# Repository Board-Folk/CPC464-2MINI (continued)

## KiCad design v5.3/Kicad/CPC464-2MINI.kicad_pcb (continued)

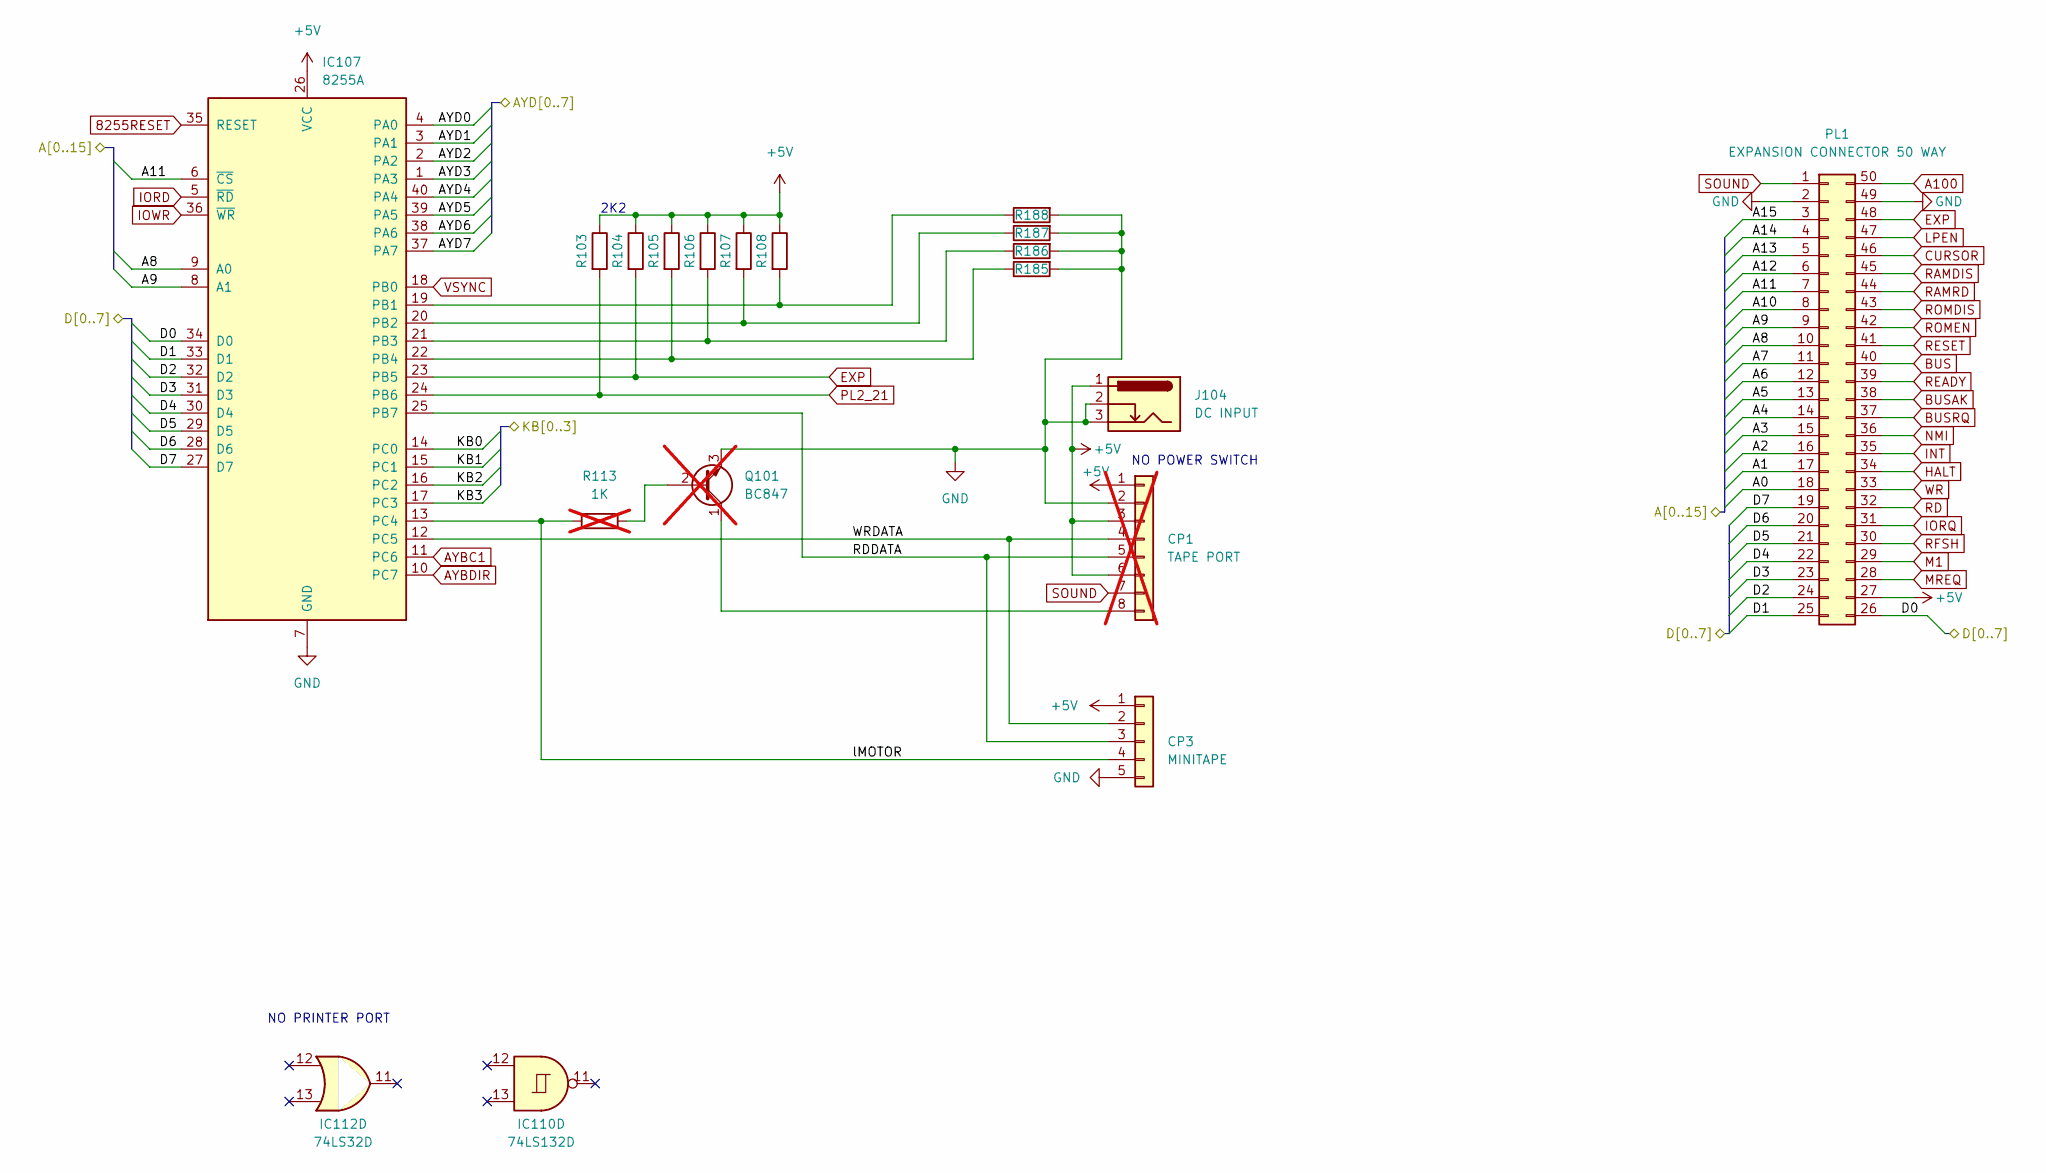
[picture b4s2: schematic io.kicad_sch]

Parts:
CP1: TAPE PORT; PinHeader_1x08_P2.54mm_Vertical; not fitted
CP3: MINITAPE; PinHeader_1x05_P2.54mm_Vertical
IC107: 8255A; DIP-40_W15.24mm
IC110: 74LS132D; SOIC-14_3.9x8.7mm_P1.27mm
IC112: 74LS32D; SOIC-14_3.9x8.7mm_P1.27mm
J104: DC INPUT; BarrelJack_Horizontal
PL1: EXPANSION CONNECTOR 50 WAY; EXPANSION_IDC_ANONYMISED
Q101: BC847; TO-92_Inline; not fitted
R103, R104, R105, R106, R107, R108: 2K2; R_0805_2012Metric; LCSC C114561
R113: 1K; R_0805_2012Metric; LCSC C482939; not fitted
R185, R186, R187, R188: 0R; R_0805_2012Metric; LCSC C114561

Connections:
8255RESET: IC107.35 (RESET); also elsewhere on the board
+5V: CP1.1, CP1.3, CP1.6, CP3.1, IC107.26 (VCC), J104.1, PL1.27, R103.1, R104.1, R105.1, R106.1, R107.1, R108.1; also elsewhere on the board
/CPU/A0: PL1.18; also elsewhere on the board
/CPU/A1: PL1.17; also elsewhere on the board
/CPU/A2: PL1.16; also elsewhere on the board
/CPU/A3: PL1.15; also elsewhere on the board
/CPU/A4: PL1.14; also elsewhere on the board
/CPU/A5: PL1.13; also elsewhere on the board
/CPU/A6: PL1.12; also elsewhere on the board
/CPU/A7: PL1.11; also elsewhere on the board
/CPU/A8: IC107.9 (A0), PL1.10; also elsewhere on the board
/CPU/A9: IC107.8 (A1), PL1.9; also elsewhere on the board
/CPU/A10: PL1.8; also elsewhere on the board
/CPU/A11: IC107.6 (~CS), PL1.7; also elsewhere on the board
/CPU/A12: PL1.6; also elsewhere on the board
/CPU/A13: PL1.5; also elsewhere on the board
/CPU/A14: PL1.4; also elsewhere on the board
/CPU/A15: PL1.3; also elsewhere on the board
/CPU/D0: IC107.34 (D0), PL1.26; also elsewhere on the board
/CPU/D1: IC107.33 (D1), PL1.25; also elsewhere on the board
/CPU/D2: IC107.32 (D2), PL1.24; also elsewhere on the board
/CPU/D3: IC107.31 (D3), PL1.23; also elsewhere on the board
/CPU/D4: IC107.30 (D4), PL1.22; also elsewhere on the board
/CPU/D5: IC107.29 (D5), PL1.21; also elsewhere on the board
/CPU/D6: IC107.28 (D6), PL1.20; also elsewhere on the board
/CPU/D7: IC107.27 (D7), PL1.19; also elsewhere on the board
/IO/AYD0: IC107.4 (PA0); also elsewhere on the board
/IO/AYD1: IC107.3 (PA1); also elsewhere on the board
/IO/AYD2: IC107.2 (PA2); also elsewhere on the board
/IO/AYD3: IC107.1 (PA3); also elsewhere on the board
/IO/AYD4: IC107.40 (PA4); also elsewhere on the board
/IO/AYD5: IC107.39 (PA5); also elsewhere on the board
/IO/AYD6: IC107.38 (PA6); also elsewhere on the board
/IO/AYD7: IC107.37 (PA7); also elsewhere on the board
/IO/KB0: IC107.14 (PC0); also elsewhere on the board
/IO/KB1: IC107.15 (PC1); also elsewhere on the board
/IO/KB2: IC107.16 (PC2); also elsewhere on the board
/IO/KB3: IC107.17 (PC3); also elsewhere on the board
/IO/RDDATA: CP1.5, CP3.3, IC107.25 (PB7)
/IO/WRDATA: CP1.4, CP3.2, IC107.12 (PC5)
/IO/lMOTOR: CP3.4, IC107.13 (PC4), R113.1
A100: PL1.50; also elsewhere on the board
AYBC1: IC107.11 (PC6); also elsewhere on the board
AYBDIR: IC107.10 (PC7); also elsewhere on the board
BUS: PL1.40; also elsewhere on the board
BUSAK: PL1.38; also elsewhere on the board
BUSRQ: PL1.37; also elsewhere on the board
CURSOR: PL1.46; also elsewhere on the board
EXP: IC107.23 (PB5), PL1.48, R104.2
GND: CP1.2, CP3.5, IC107.7 (GND), J104.2, J104.3, PL1.2, PL1.49, Q101.3 (E), R185.2, R186.2, R187.2, R188.2; also elsewhere on the board
HALT: PL1.34; also elsewhere on the board
INT: PL1.35; also elsewhere on the board
IORD: IC107.5 (~RD); also elsewhere on the board
IORQ: PL1.31; also elsewhere on the board
IOWR: IC107.36 (~WR); also elsewhere on the board
LPEN: PL1.47; also elsewhere on the board
M1: PL1.29; also elsewhere on the board
MREQ: PL1.28; also elsewhere on the board
NMI: PL1.36; also elsewhere on the board
unnamed: CP1.8, Q101.1 (C)
unnamed: IC107.19 (PB1), R108.2, R188.1
unnamed: IC107.20 (PB2), R107.2, R187.1
unnamed: IC107.21 (PB3), R106.2, R186.1
unnamed: IC107.22 (PB4), R105.2, R185.1
unnamed: Q101.2 (B), R113.2
PL2_21: IC107.24 (PB6), R103.2
RAMDIS: PL1.45; also elsewhere on the board
RAMRD: PL1.44; also elsewhere on the board
RD: PL1.32; also elsewhere on the board
READY: PL1.39; also elsewhere on the board
RESET: PL1.41; also elsewhere on the board
RFSH: PL1.30; also elsewhere on the board
ROMDIS: PL1.43; also elsewhere on the board
ROMEN: PL1.42; also elsewhere on the board
SOUND: CP1.7, PL1.1; also elsewhere on the board
VSYNC: IC107.18 (PB0); also elsewhere on the board
WR: PL1.33; also elsewhere on the board

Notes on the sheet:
2K2
NO POWER SWITCH
NO PRINTER PORT

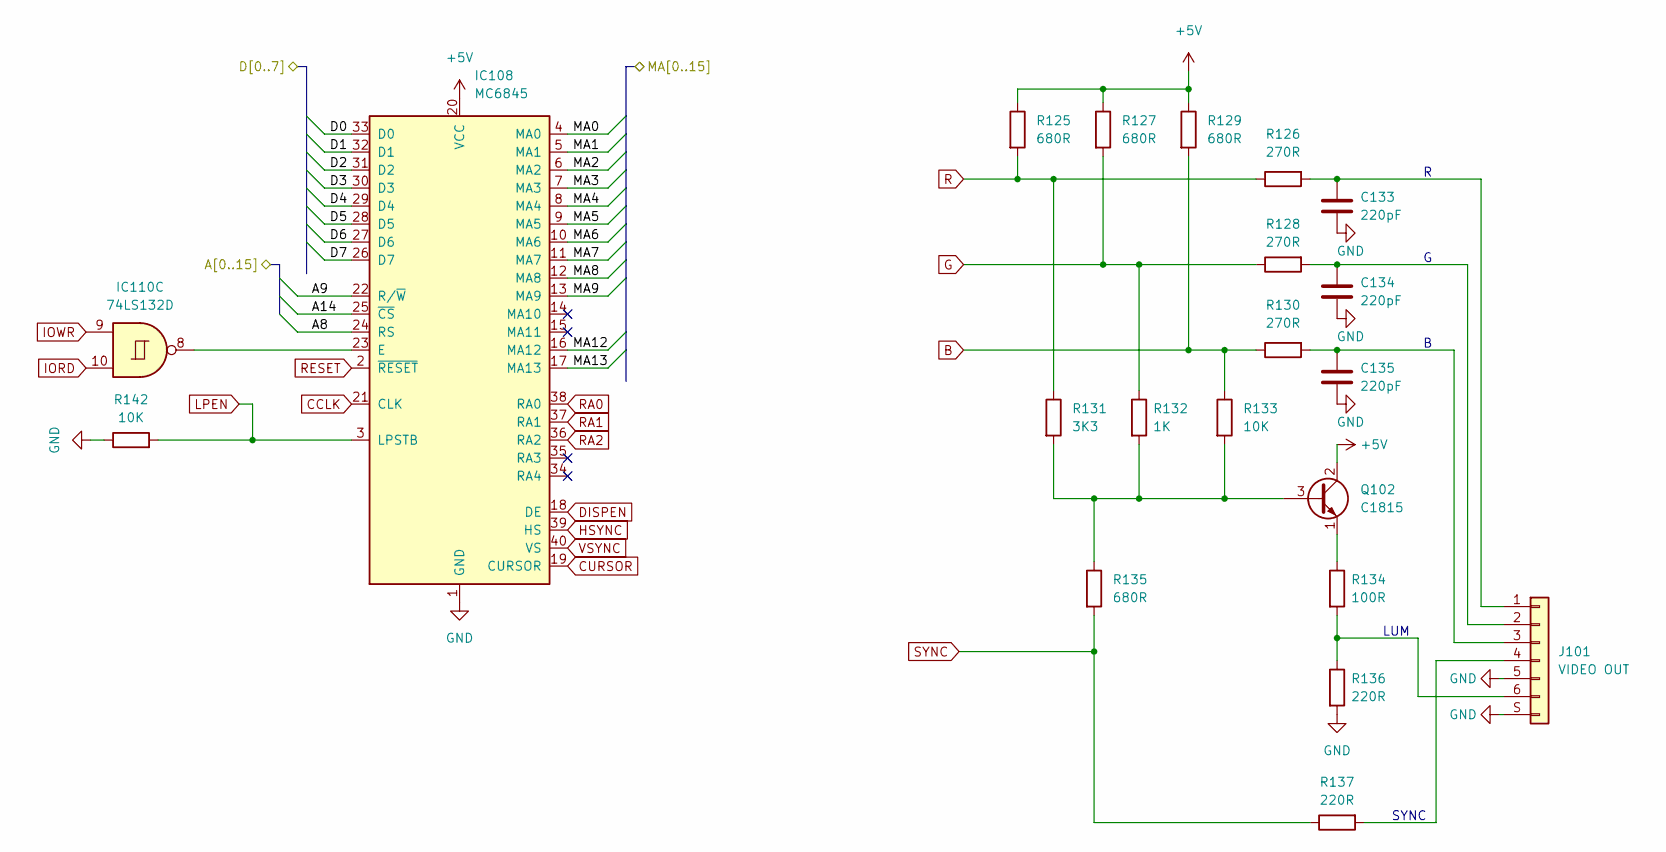
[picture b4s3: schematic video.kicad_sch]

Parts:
C133, C134, C135: 220pF; C_0805_2012Metric; LCSC C1727
IC108: MC6845; DIP-40_W15.24mm
IC110: 74LS132D; SOIC-14_3.9x8.7mm_P1.27mm
J101: VIDEO OUT; VIDEOJACK
Q102: C1815; SOT-23
R125, R127, R129, R135: 680R; R_0805_2012Metric; LCSC C114549
R126, R128, R130: 270R; R_0805_2012Metric; LCSC C137558
R131: 3K3; R_0805_2012Metric; LCSC C114531
R132: 1K; R_0805_2012Metric; LCSC C482939
R133, R142: 10K; R_0805_2012Metric; LCSC C84376
R134: 100R; R_0805_2012Metric; LCSC C105577
R136, R137: 220R; R_0805_2012Metric; LCSC C114519

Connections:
+5V: IC108.20 (VCC), Q102.2 (C), R125.1, R127.1, R129.1; also elsewhere on the board
/CPU/A8: IC108.24 (RS); also elsewhere on the board
/CPU/A9: IC108.22 (R/~W); also elsewhere on the board
/CPU/A14: IC108.25 (~CS); also elsewhere on the board
/CPU/D0: IC108.33 (D0); also elsewhere on the board
/CPU/D1: IC108.32 (D1); also elsewhere on the board
/CPU/D2: IC108.31 (D2); also elsewhere on the board
/CPU/D3: IC108.30 (D3); also elsewhere on the board
/CPU/D4: IC108.29 (D4); also elsewhere on the board
/CPU/D5: IC108.28 (D5); also elsewhere on the board
/CPU/D6: IC108.27 (D6); also elsewhere on the board
/CPU/D7: IC108.26 (D7); also elsewhere on the board
/Multiplex/MA0: IC108.4 (MA0); also elsewhere on the board
/Multiplex/MA1: IC108.5 (MA1); also elsewhere on the board
/Multiplex/MA2: IC108.6 (MA2); also elsewhere on the board
/Multiplex/MA3: IC108.7 (MA3); also elsewhere on the board
/Multiplex/MA4: IC108.8 (MA4); also elsewhere on the board
/Multiplex/MA5: IC108.9 (MA5); also elsewhere on the board
/Multiplex/MA6: IC108.10 (MA6); also elsewhere on the board
/Multiplex/MA7: IC108.11 (MA7); also elsewhere on the board
/Multiplex/MA8: IC108.12 (MA8); also elsewhere on the board
/Multiplex/MA9: IC108.13 (MA9); also elsewhere on the board
/Multiplex/MA12: IC108.16 (MA12); also elsewhere on the board
/Multiplex/MA13: IC108.17 (MA13); also elsewhere on the board
B: R129.2, R130.1, R133.1; also elsewhere on the board
CCLK: IC108.21 (CLK); also elsewhere on the board
CURSOR: IC108.19 (CURSOR); also elsewhere on the board
DISPEN: IC108.18 (DE); also elsewhere on the board
G: R127.2, R128.1, R132.1; also elsewhere on the board
GND: C133.2, C134.2, C135.2, IC108.1 (GND), J101.5, J101.S (Shield), R136.2, R142.1; also elsewhere on the board
HSYNC: IC108.39 (HS); also elsewhere on the board
IORD: IC110.10; also elsewhere on the board
IOWR: IC110.9; also elsewhere on the board
LPEN: IC108.3 (LPSTB), R142.2; also elsewhere on the board
unnamed: IC108.23 (E), IC110.8
unnamed: C133.1, J101.1, R126.2
unnamed: C134.1, J101.2, R128.2
unnamed: C135.1, J101.3, R130.2
unnamed: J101.4, R137.2
unnamed: J101.6, R134.2, R136.1
unnamed: Q102.3 (B), R131.2, R132.2, R133.2, R135.1
unnamed: Q102.1 (E), R134.1
R: R125.2, R126.1, R131.1; also elsewhere on the board
RA0: IC108.38 (RA0); also elsewhere on the board
RA1: IC108.37 (RA1); also elsewhere on the board
RA2: IC108.36 (RA2); also elsewhere on the board
RESET: IC108.2 (~RESET); also elsewhere on the board
SYNC: R135.2, R137.1; also elsewhere on the board
VSYNC: IC108.40 (VS); also elsewhere on the board

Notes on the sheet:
LUM
SYNC

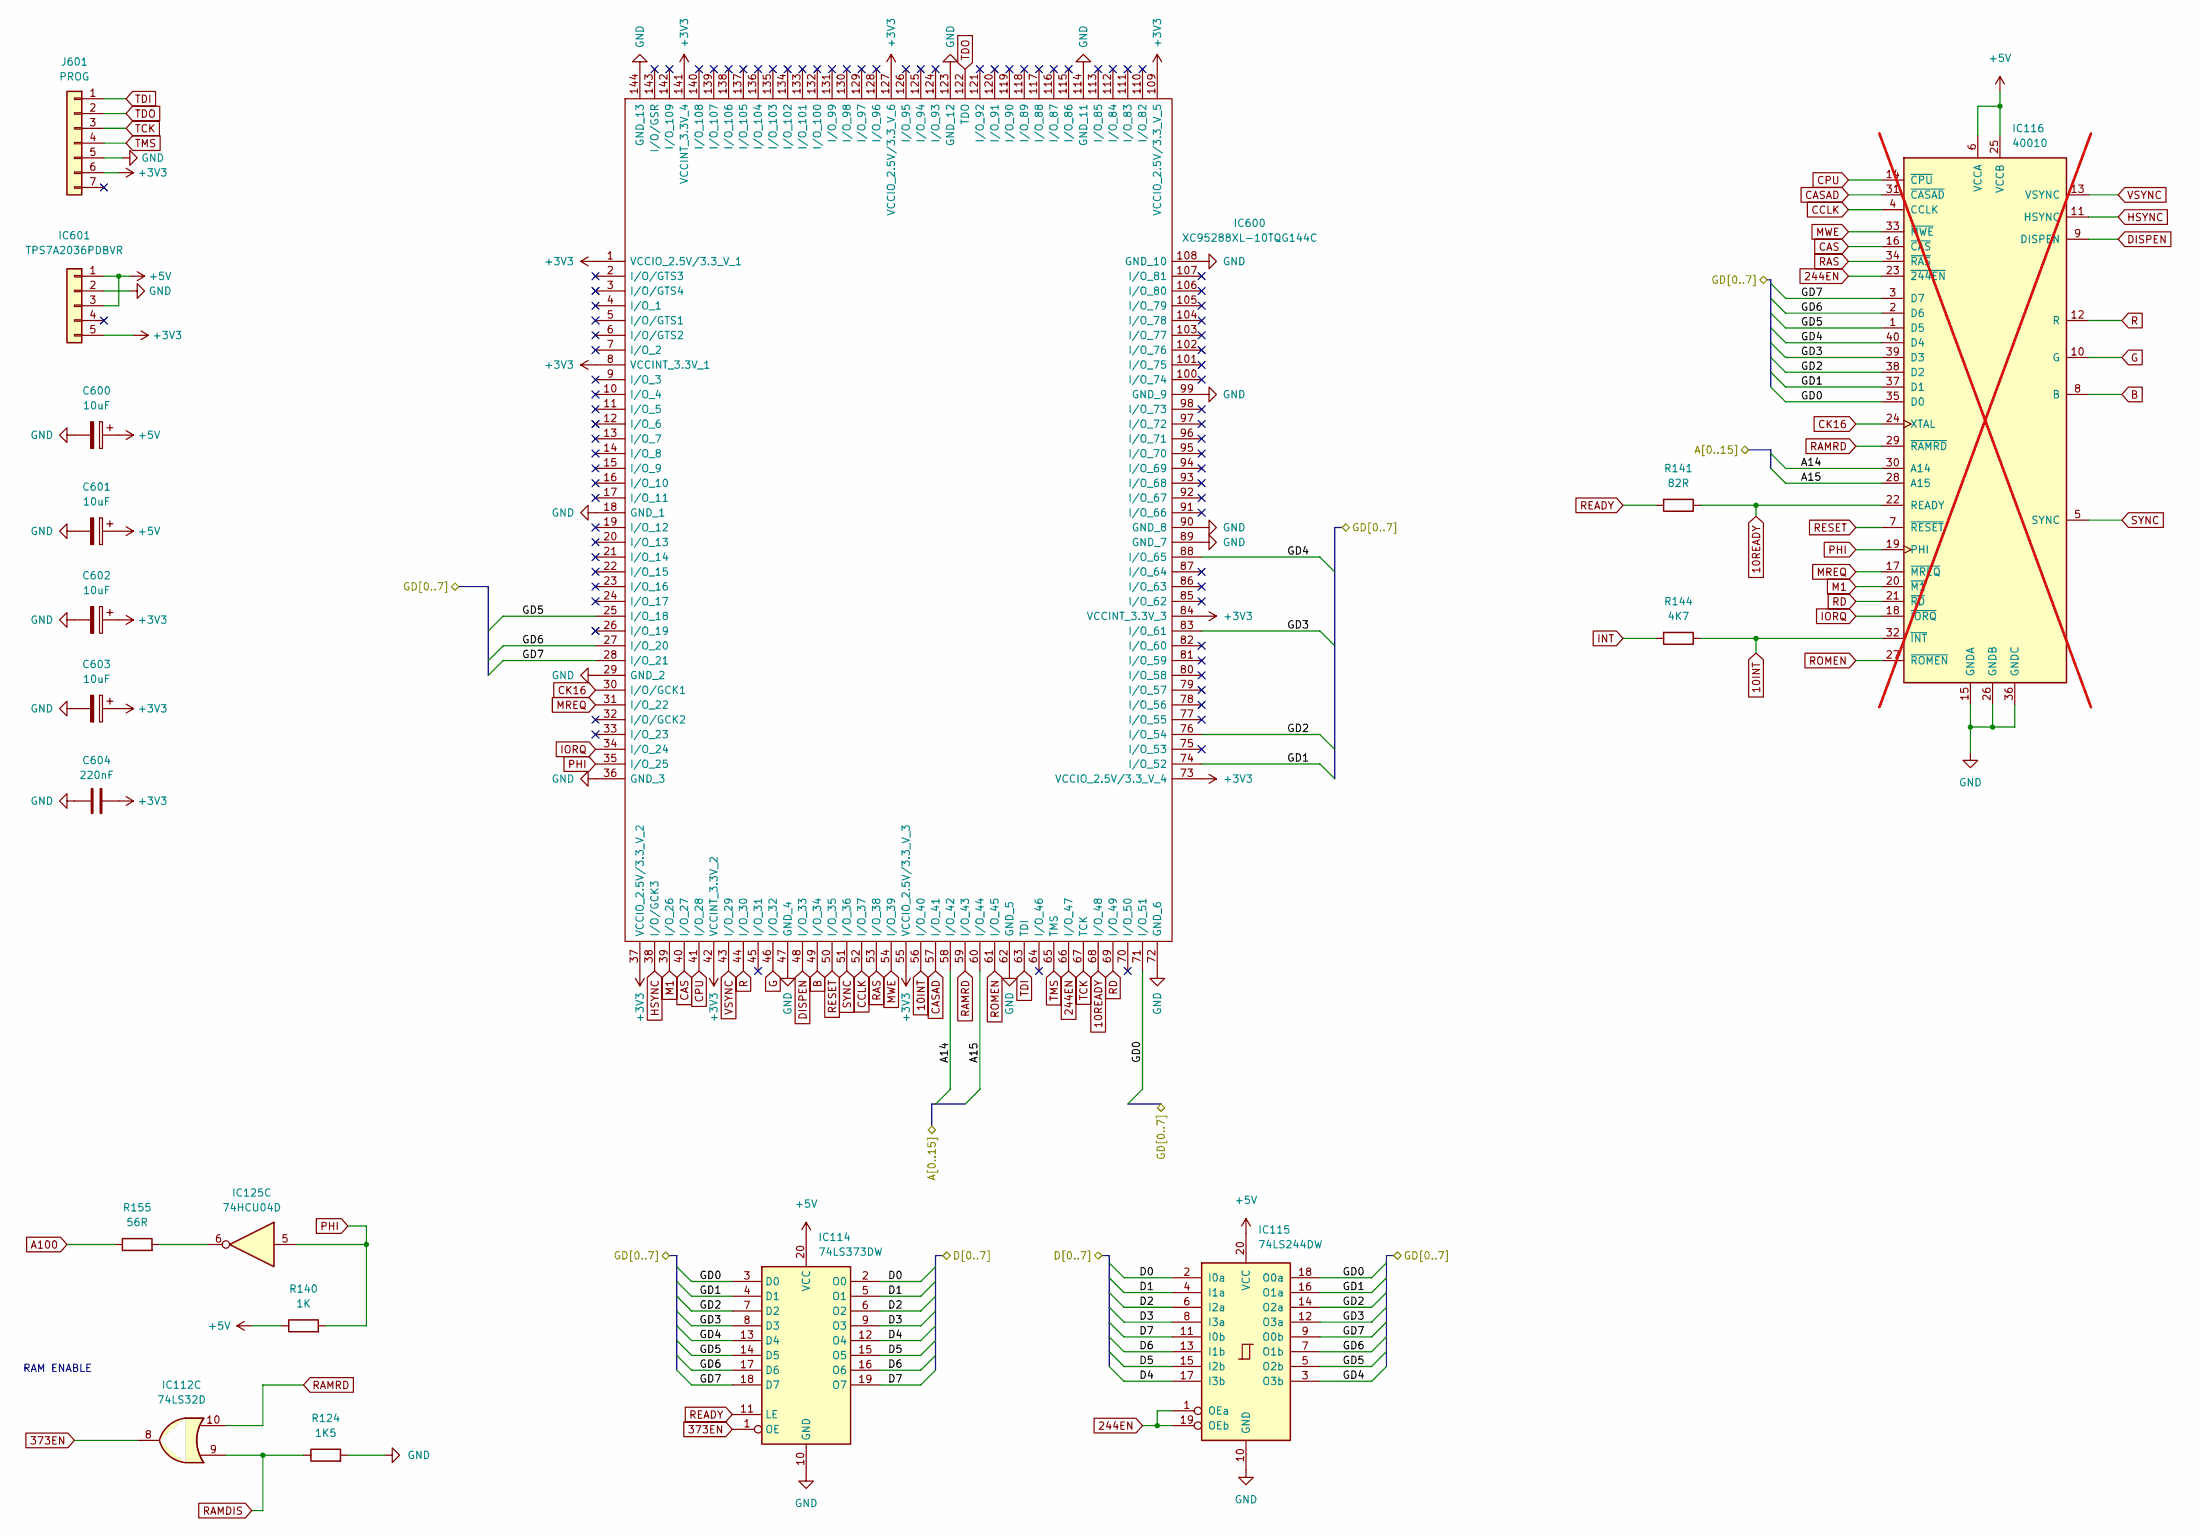
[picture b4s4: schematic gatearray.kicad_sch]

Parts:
C600, C601, C602, C603: 10uF; CP_EIA-3216-18_Kemet-A
C604: 220nF; R_0805_2012Metric
IC112: 74LS32D; SOIC-14_3.9x8.7mm_P1.27mm
IC114: 74LS373DW; SOIC-20W_7.5x12.8mm_P1.27mm
IC115: 74LS244DW; SOIC-20W_7.5x12.8mm_P1.27mm
IC116: 40010; DIP-40_W15.24mm; not fitted
IC125: 74HCU04D; SOIC-14_3.9x8.7mm_P1.27mm
IC600: XC95288XL-10TQG144C; QFP50P2200X2200X160-144N; Mouser Part Number 217-5288XL-10TQG144C
IC601: TPS7A2036PDBVR; SOT-23-5
J601: PROG; PinHeader_1x07_P2.54mm_Vertical
R124: 1K5; R_0805_2012Metric; LCSC C114555
R140: 1K; R_0805_2012Metric; LCSC C482939
R141: 82R; R_0805_2012Metric; LCSC C706251
R144: 4K7; R_0805_2012Metric; LCSC C60816
R155: 56R; R_0805_2012Metric; LCSC C144135

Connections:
10INT: IC116.32 (~INT), IC600.56 (I/O_40), R144.1
10READY: IC116.22 (READY), IC600.68 (I/O_48), R141.1
244EN: IC115.1 (OEa), IC115.19 (OEb), IC116.23 (~244EN), IC600.66 (I/O_47)
373EN: IC112.8, IC114.1 (OE)
+3V3: C602.1, C603.1, C604.2, IC600.1 (VCCIO_2.5V/3.3_V_1), IC600.8 (VCCINT_3.3V_1), IC600.37 (VCCIO_2.5V/3.3_V_2), IC600.42 (VCCINT_3.3V_2), IC600.55 (VCCIO_2.5V/3.3_V_3), IC600.73 (VCCIO_2.5V/3.3_V_4), IC600.84 (VCCINT_3.3V_3), IC600.109 (VCCIO_2.5V/3.3_V_5), IC600.127 (VCCIO_2.5V/3.3_V_6), IC600.141 (VCCINT_3.3V_4), IC601.5, J601.6
+5V: C600.1, C601.1, IC114.20 (VCC), IC115.20 (VCC), IC116.6 (VCCA), IC116.25 (VCCB), IC601.1, IC601.3, R140.1; also elsewhere on the board
/CPU/A14: IC116.30 (A14), IC600.58 (I/O_42); also elsewhere on the board
/CPU/A15: IC116.28 (A15), IC600.60 (I/O_44); also elsewhere on the board
/CPU/D0: IC114.2 (O0), IC115.2 (I0a); also elsewhere on the board
/CPU/D1: IC114.5 (O1), IC115.4 (I1a); also elsewhere on the board
/CPU/D2: IC114.6 (O2), IC115.6 (I2a); also elsewhere on the board
/CPU/D3: IC114.9 (O3), IC115.8 (I3a); also elsewhere on the board
/CPU/D4: IC114.12 (O4), IC115.17 (I3b); also elsewhere on the board
/CPU/D5: IC114.15 (O5), IC115.15 (I2b); also elsewhere on the board
/CPU/D6: IC114.16 (O6), IC115.13 (I1b); also elsewhere on the board
/CPU/D7: IC114.19 (O7), IC115.11 (I0b); also elsewhere on the board
/Gate Arrays/GD0: IC114.3 (D0), IC115.18 (O0a), IC116.35 (D0), IC600.71 (I/O_51); also elsewhere on the board
/Gate Arrays/GD1: IC114.4 (D1), IC115.16 (O1a), IC116.37 (D1), IC600.74 (I/O_52); also elsewhere on the board
/Gate Arrays/GD2: IC114.7 (D2), IC115.14 (O2a), IC116.38 (D2), IC600.76 (I/O_54); also elsewhere on the board
/Gate Arrays/GD3: IC114.8 (D3), IC115.12 (O3a), IC116.39 (D3), IC600.83 (I/O_61); also elsewhere on the board
/Gate Arrays/GD4: IC114.13 (D4), IC115.3 (O3b), IC116.40 (D4), IC600.88 (I/O_65); also elsewhere on the board
/Gate Arrays/GD5: IC114.14 (D5), IC115.5 (O2b), IC116.1 (D5), IC600.25 (I/O_18); also elsewhere on the board
/Gate Arrays/GD6: IC114.17 (D6), IC115.7 (O1b), IC116.2 (D6), IC600.27 (I/O_20); also elsewhere on the board
/Gate Arrays/GD7: IC114.18 (D7), IC115.9 (O0b), IC116.3 (D7), IC600.28 (I/O_21); also elsewhere on the board
A100: R155.1; also elsewhere on the board
B: IC116.8 (B), IC600.49 (I/O_34); also elsewhere on the board
CAS: IC116.16 (~CAS), IC600.40 (I/O_27); also elsewhere on the board
CASAD: IC116.31 (~CASAD), IC600.57 (I/O_41); also elsewhere on the board
CCLK: IC116.4 (CCLK), IC600.52 (I/O_37); also elsewhere on the board
CK16: IC116.24 (XTAL), IC600.30 (I/O/GCK1); also elsewhere on the board
CPU: IC116.14 (~CPU), IC600.41 (I/O_28); also elsewhere on the board
DISPEN: IC116.9 (DISPEN), IC600.48 (I/O_33); also elsewhere on the board
G: IC116.10 (G), IC600.46 (I/O_32); also elsewhere on the board
GND: C600.2, C601.2, C602.2, C603.2, C604.1, IC114.10 (GND), IC115.10 (GND), IC116.15 (GNDA), IC116.26 (GNDB), IC116.36 (GNDC), IC600.18 (GND_1), IC600.29 (GND_2), IC600.36 (GND_3), IC600.47 (GND_4), IC600.62 (GND_5), IC600.72 (GND_6), IC600.89 (GND_7), IC600.90 (GND_8), IC600.99 (GND_9), IC600.108 (GND_10), IC600.114 (GND_11), IC600.123 (GND_12), IC600.144 (GND_13), IC601.2, J601.5, R124.2; also elsewhere on the board
HSYNC: IC116.11 (HSYNC), IC600.38 (I/O/GCK3); also elsewhere on the board
INT: R144.2; also elsewhere on the board
IORQ: IC116.18 (~IORQ), IC600.34 (I/O_24); also elsewhere on the board
M1: IC116.20 (~M1), IC600.39 (I/O_26); also elsewhere on the board
MREQ: IC116.17 (~MREQ), IC600.31 (I/O_22); also elsewhere on the board
MWE: IC116.33 (~MWE), IC600.54 (I/O_39); also elsewhere on the board
unnamed: IC125.6, R155.2
PHI: IC116.19 (PHI), IC125.5, IC600.35 (I/O_25), R140.2
R: IC116.12 (R), IC600.44 (I/O_30); also elsewhere on the board
RAMDIS: IC112.9, R124.1; also elsewhere on the board
RAMRD: IC112.10, IC116.29 (~RAMRD), IC600.59 (I/O_43); also elsewhere on the board
RAS: IC116.34 (~RAS), IC600.53 (I/O_38); also elsewhere on the board
RD: IC116.21 (~RD), IC600.69 (I/O_49); also elsewhere on the board
READY: IC114.11 (LE), R141.2; also elsewhere on the board
RESET: IC116.7 (~RESET), IC600.50 (I/O_35); also elsewhere on the board
ROMEN: IC116.27 (~ROMEN), IC600.61 (I/O_45); also elsewhere on the board
SYNC: IC116.5 (SYNC), IC600.51 (I/O_36); also elsewhere on the board
TCK: IC600.67 (TCK), J601.3
TDI: IC600.63 (TDI), J601.1
TDO: IC600.122 (TDO), J601.2
TMS: IC600.65 (TMS), J601.4
VSYNC: IC116.13 (VSYNC), IC600.43 (I/O_29); also elsewhere on the board

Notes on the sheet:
RAM ENABLE

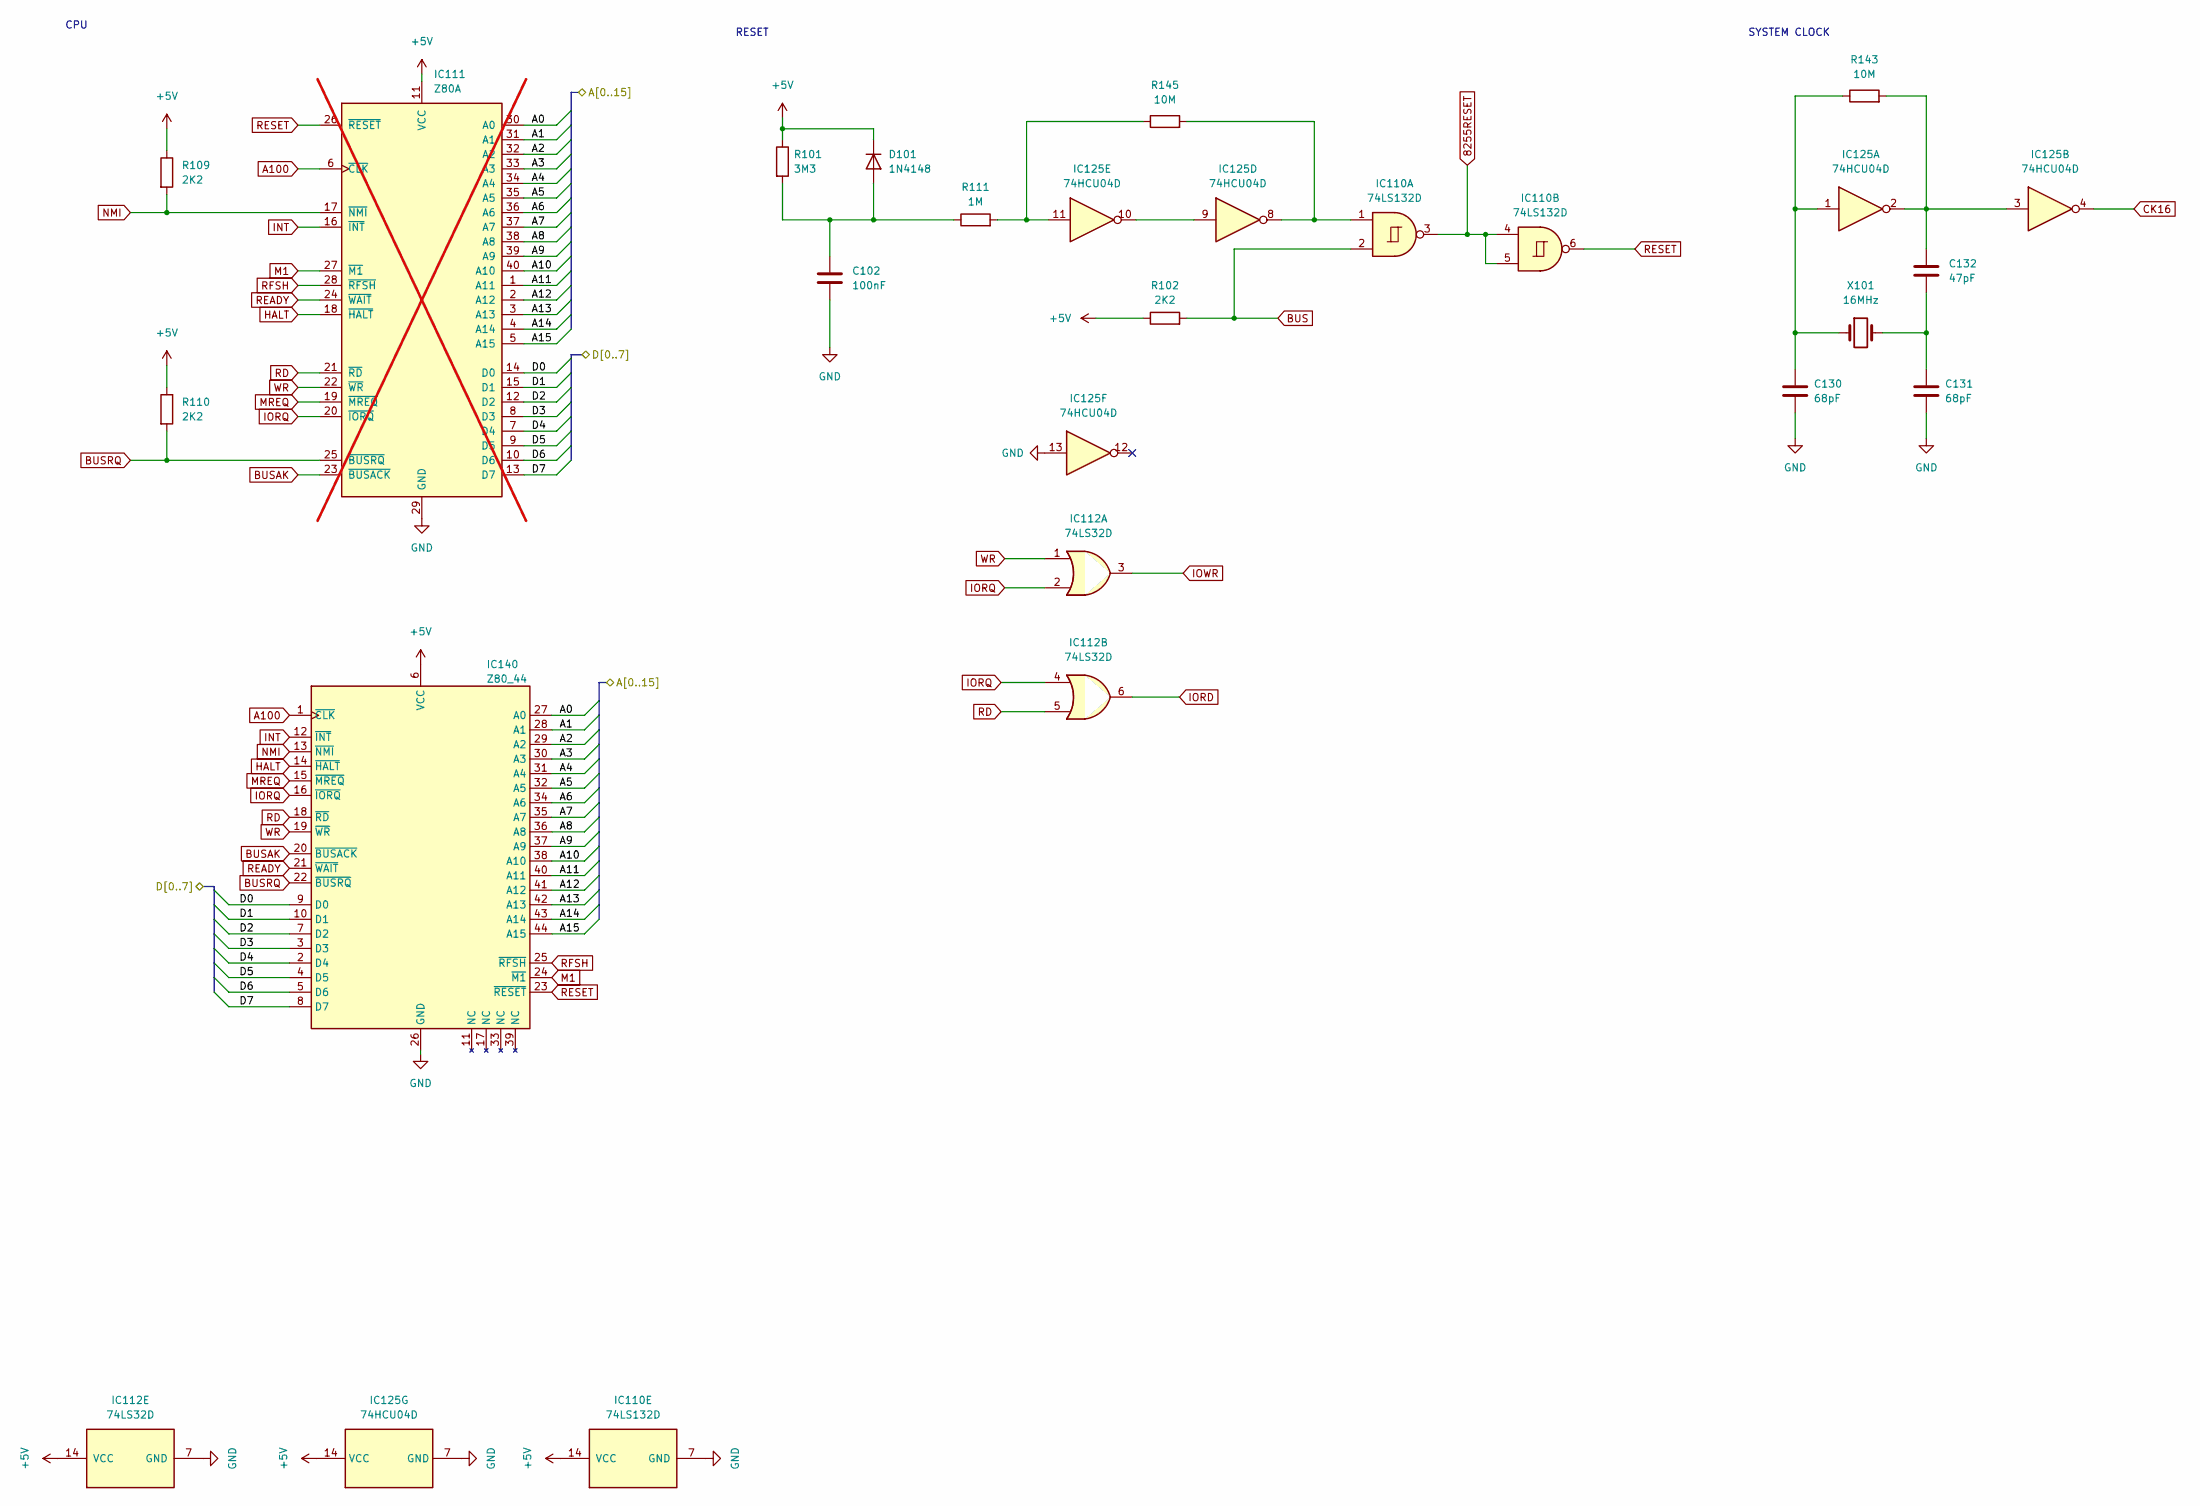
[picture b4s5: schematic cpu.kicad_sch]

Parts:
C102: 100nF; C_0805_2012Metric; LCSC C49678
C130, C131: 68pF; C_0805_2012Metric; LCSC C1834
C132: 47pF; C_0805_2012Metric; LCSC C24659
D101: 1N4148; D101; LCSC C2099
IC110: 74LS132D; SOIC-14_3.9x8.7mm_P1.27mm
IC111: Z80A; DIP-40_W15.24mm; not fitted
IC112: 74LS32D; SOIC-14_3.9x8.7mm_P1.27mm
IC125: 74HCU04D; SOIC-14_3.9x8.7mm_P1.27mm
IC140: Z80_44; LQFP-44_10x10mm_P0.8mm
R101: 3M3; R_0805_2012Metric; LCSC C483095
R102, R109, R110: 2K2; R_0805_2012Metric; LCSC C114561
R111: 1M; R_0805_2012Metric; LCSC C482940
R143, R145: 10M; R_0805_2012Metric; LCSC C309665
X101: 16MHz; Crystal_HC49-U_Vertical

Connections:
8255RESET: IC110.3, IC110.4, IC110.5; also elsewhere on the board
+5V: D101.1 (K), IC110.14 (VCC), IC111.11 (VCC), IC112.14 (VCC), IC125.14 (VCC), IC140.6 (VCC), R101.1, R102.1, R109.1, R110.1; also elsewhere on the board
/CPU/A0: IC111.30 (A0), IC140.27 (A0); also elsewhere on the board
/CPU/A1: IC111.31 (A1), IC140.28 (A1); also elsewhere on the board
/CPU/A2: IC111.32 (A2), IC140.29 (A2); also elsewhere on the board
/CPU/A3: IC111.33 (A3), IC140.30 (A3); also elsewhere on the board
/CPU/A4: IC111.34 (A4), IC140.31 (A4); also elsewhere on the board
/CPU/A5: IC111.35 (A5), IC140.32 (A5); also elsewhere on the board
/CPU/A6: IC111.36 (A6), IC140.34 (A6); also elsewhere on the board
/CPU/A7: IC111.37 (A7), IC140.35 (A7); also elsewhere on the board
/CPU/A8: IC111.38 (A8), IC140.36 (A8); also elsewhere on the board
/CPU/A9: IC111.39 (A9), IC140.37 (A9); also elsewhere on the board
/CPU/A10: IC111.40 (A10), IC140.38 (A10); also elsewhere on the board
/CPU/A11: IC111.1 (A11), IC140.40 (A11); also elsewhere on the board
/CPU/A12: IC111.2 (A12), IC140.41 (A12); also elsewhere on the board
/CPU/A13: IC111.3 (A13), IC140.42 (A13); also elsewhere on the board
/CPU/A14: IC111.4 (A14), IC140.43 (A14); also elsewhere on the board
/CPU/A15: IC111.5 (A15), IC140.44 (A15); also elsewhere on the board
/CPU/D0: IC111.14 (D0), IC140.9 (D0); also elsewhere on the board
/CPU/D1: IC111.15 (D1), IC140.10 (D1); also elsewhere on the board
/CPU/D2: IC111.12 (D2), IC140.7 (D2); also elsewhere on the board
/CPU/D3: IC111.8 (D3), IC140.3 (D3); also elsewhere on the board
/CPU/D4: IC111.7 (D4), IC140.2 (D4); also elsewhere on the board
/CPU/D5: IC111.9 (D5), IC140.4 (D5); also elsewhere on the board
/CPU/D6: IC111.10 (D6), IC140.5 (D6); also elsewhere on the board
/CPU/D7: IC111.13 (D7), IC140.8 (D7); also elsewhere on the board
A100: IC111.6 (~CLK), IC140.1 (~CLK); also elsewhere on the board
BUS: IC110.2, R102.2; also elsewhere on the board
BUSAK: IC111.23 (~BUSACK), IC140.20 (~BUSACK); also elsewhere on the board
BUSRQ: IC111.25 (~BUSRQ), IC140.22 (~BUSRQ), R110.2; also elsewhere on the board
CK16: IC125.4; also elsewhere on the board
GND: C102.2, C130.2, C131.2, IC110.7 (GND), IC111.29 (GND), IC112.7 (GND), IC125.7 (GND), IC125.13, IC140.26 (GND); also elsewhere on the board
HALT: IC111.18 (~HALT), IC140.14 (~HALT); also elsewhere on the board
INT: IC111.16 (~INT), IC140.12 (~INT); also elsewhere on the board
IORD: IC112.6; also elsewhere on the board
IORQ: IC111.20 (~IORQ), IC112.2, IC112.4, IC140.16 (~IORQ); also elsewhere on the board
IOWR: IC112.3; also elsewhere on the board
M1: IC111.27 (~M1), IC140.24 (~M1); also elsewhere on the board
MREQ: IC111.19 (~MREQ), IC140.15 (~MREQ); also elsewhere on the board
NMI: IC111.17 (~NMI), IC140.13 (~NMI), R109.2; also elsewhere on the board
unnamed: C130.1, IC125.1, R143.1, X101.1
unnamed: C131.1, C132.1, X101.2
unnamed: C132.2, IC125.2, IC125.3, R143.2
unnamed: C102.1, D101.2 (A), R101.2, R111.1
unnamed: IC110.1, IC125.8, R145.2
unnamed: IC125.9, IC125.10
unnamed: IC125.11, R111.2, R145.1
RD: IC111.21 (~RD), IC112.5, IC140.18 (~RD); also elsewhere on the board
READY: IC111.24 (~WAIT), IC140.21 (~WAIT); also elsewhere on the board
RESET: IC110.6, IC111.26 (~RESET), IC140.23 (~RESET); also elsewhere on the board
RFSH: IC111.28 (~RFSH), IC140.25 (~RFSH); also elsewhere on the board
WR: IC111.22 (~WR), IC112.1, IC140.19 (~WR); also elsewhere on the board

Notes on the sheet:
RESET
CPU
SYSTEM CLOCK
